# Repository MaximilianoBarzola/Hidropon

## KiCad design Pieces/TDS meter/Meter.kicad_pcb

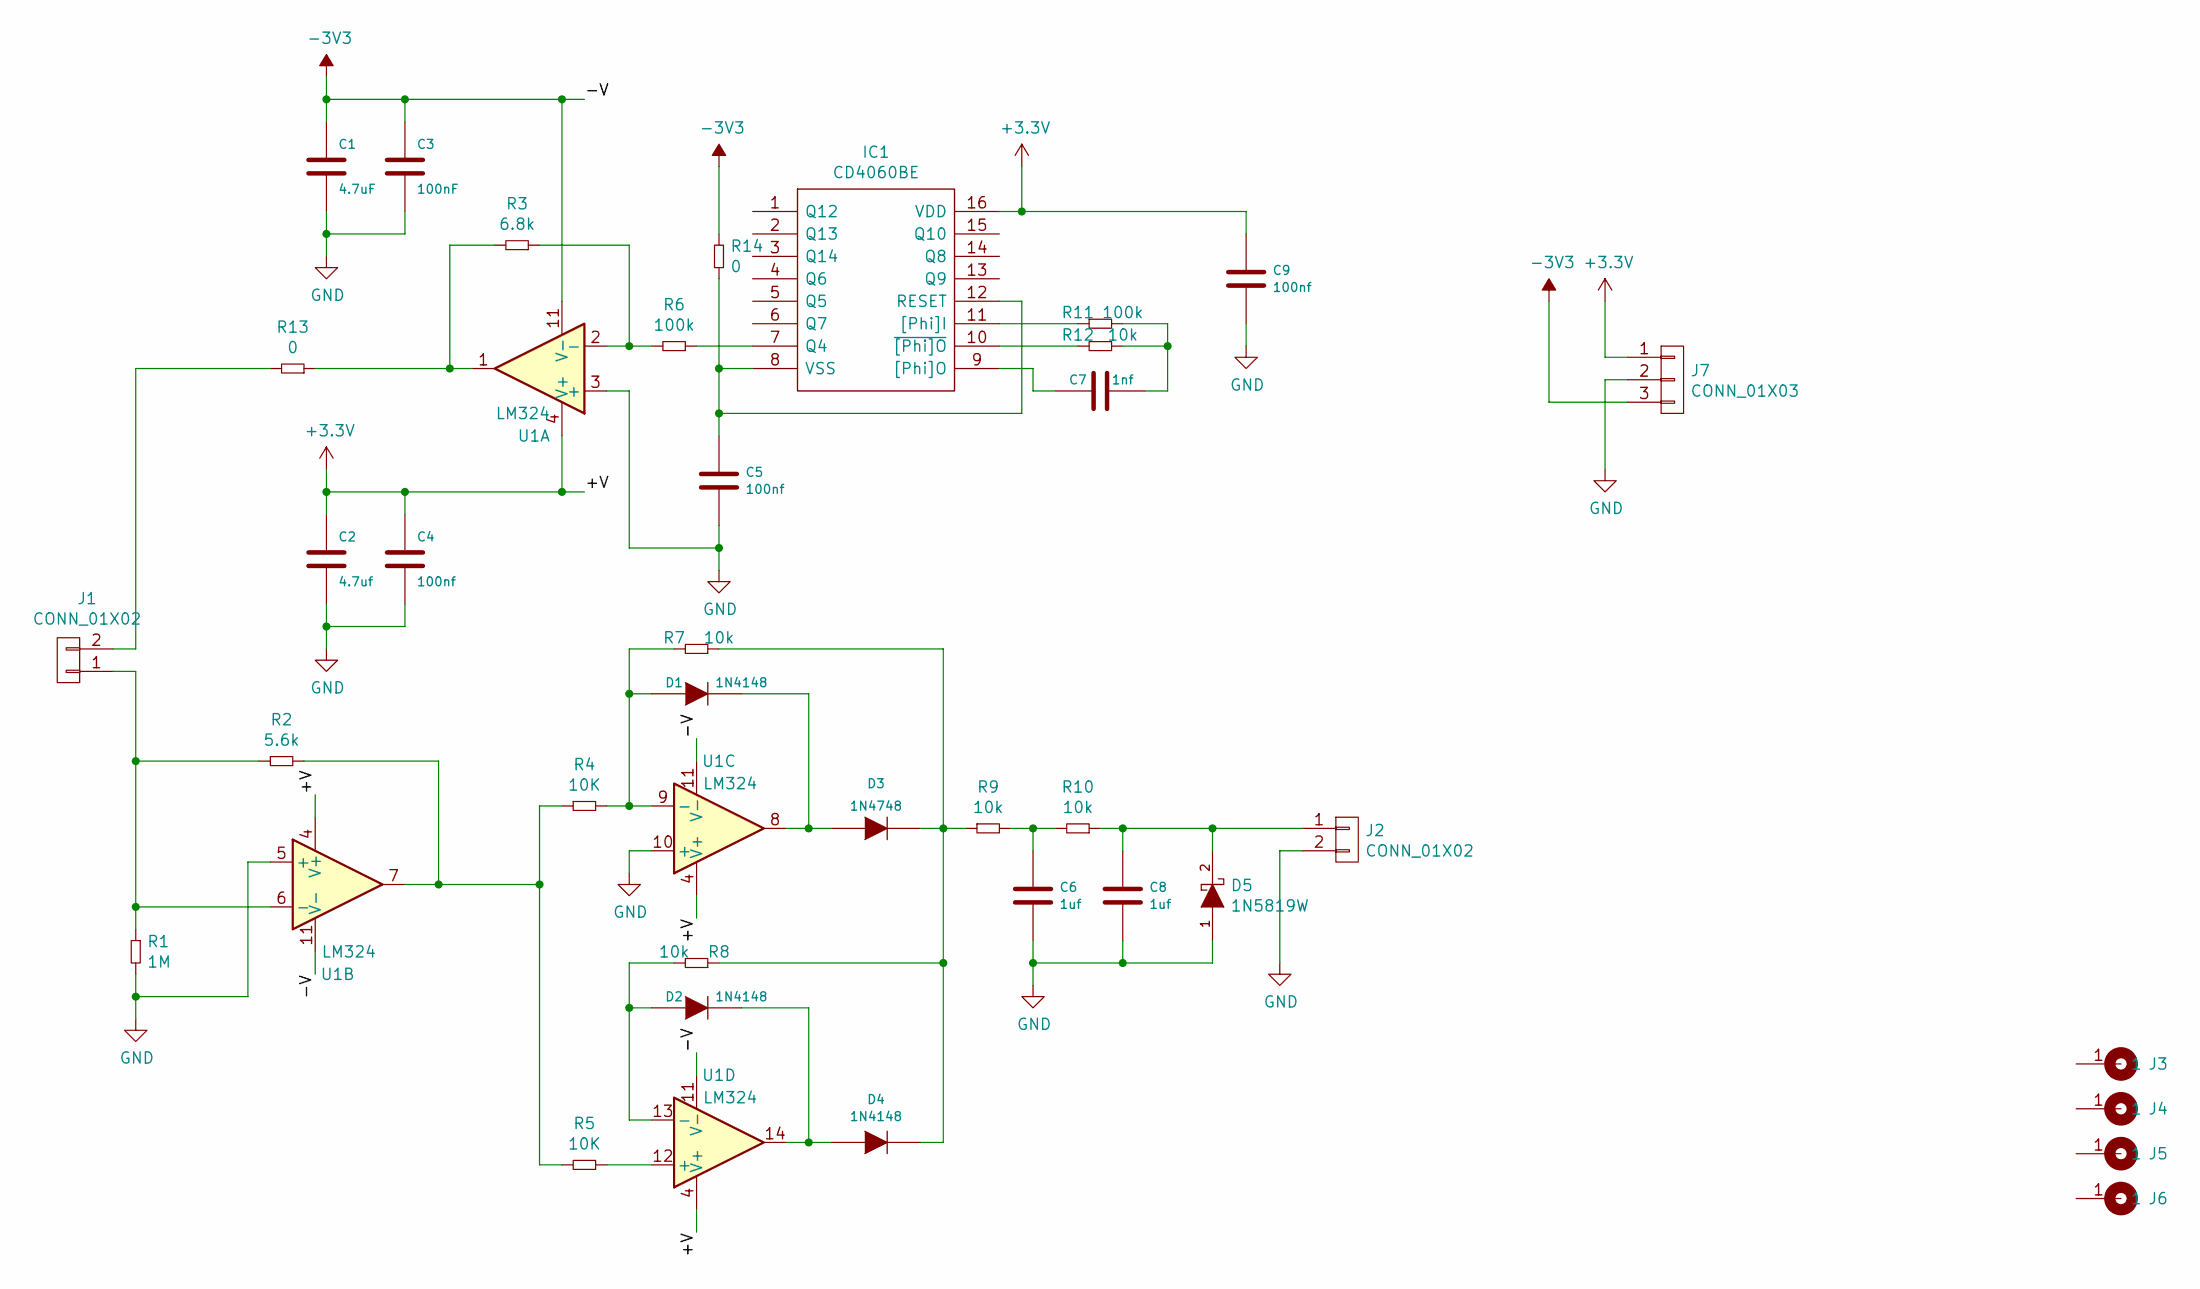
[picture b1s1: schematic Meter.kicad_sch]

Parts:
C1: 4.7uF; C_0805
C2: 4.7uf; C_0805
C3: 100nF; C_0805
C4, C5, C9: 100nf; C_0805
C6, C8: 1uf; C_0805
C7: 1nf; C_0805
D1, D2, D4: 1N4148; SOD80C
D3: 1N4748; SOD80C
D5: 1N5819W; DO-41
IC1: CD4060BE; SOP16; Manufacturer_Part_Number CD4060BE; Mouser Part Number 595-CD4060BE
J1: CONN_01X02; Pin_Strip_2_90
J2: CONN_01X02; Pin_Header_2
J3, J4, J5, J6: Cable_PAD; Tornillo_M3_8mm
J7: CONN_01X03; Pin_Strip_3
R1: 1M; R_0805
R2: 5.6k; R_0805
R3: 6.8k; R_0805
R4: 10K; R_0805
R5: 10K; RES0.3
R6, R11: 100k; R_0805
R7, R8, R9, R10, R12: 10k; R_0805
R13, R14: 0; RES0.3
U1: LM324; SOP14

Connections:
+3V3: C2.1, C4.1, C9.1, IC1.16 (VDD), J7.1, U1.4 (V+)
-3V3: C1.1, C3.1, J7.3, R14.2, U1.11 (V-)
GND: C1.2, C2.2, C3.2, C4.2, C5.2, C6.2, C8.2, C9.2, D5.1 (A), J2.2, J7.2, R1.2, U1.3 (+), U1.5 (+), U1.10 (+)
unnamed: C5.1, IC1.8 (VSS), IC1.12 (RESET), R14.1
unnamed: C6.1, R9.2, R10.2
unnamed: C7.1, R11.2, R12.1
unnamed: C7.2, IC1.9 ([Phi]O)
unnamed: C8.1, D5.2 (K), J2.1, R10.1
unnamed: D1.1 (A), R4.2, R7.2, U1.9 (-)
unnamed: D1.2 (K), D3.1 (A), U1.8
unnamed: D2.1 (A), R8.2, U1.13 (-)
unnamed: D2.2 (K), D4.1 (A), U1.14
unnamed: D3.2 (K), D4.2 (K), R7.1, R8.1, R9.1
unnamed: IC1.7 (Q4), R6.1
unnamed: IC1.10 (~[Phi]O), R12.2
unnamed: IC1.11 ([Phi]I), R11.1
unnamed: J1.1, R1.1, R2.1, U1.6 (-)
unnamed: J1.2, R13.2
unnamed: R2.2, R4.1, R5.2, U1.7
unnamed: R3.1, R6.2, U1.2 (-)
unnamed: R5.1, U1.12 (+)
unnamed: R3.2, R13.1, U1.1

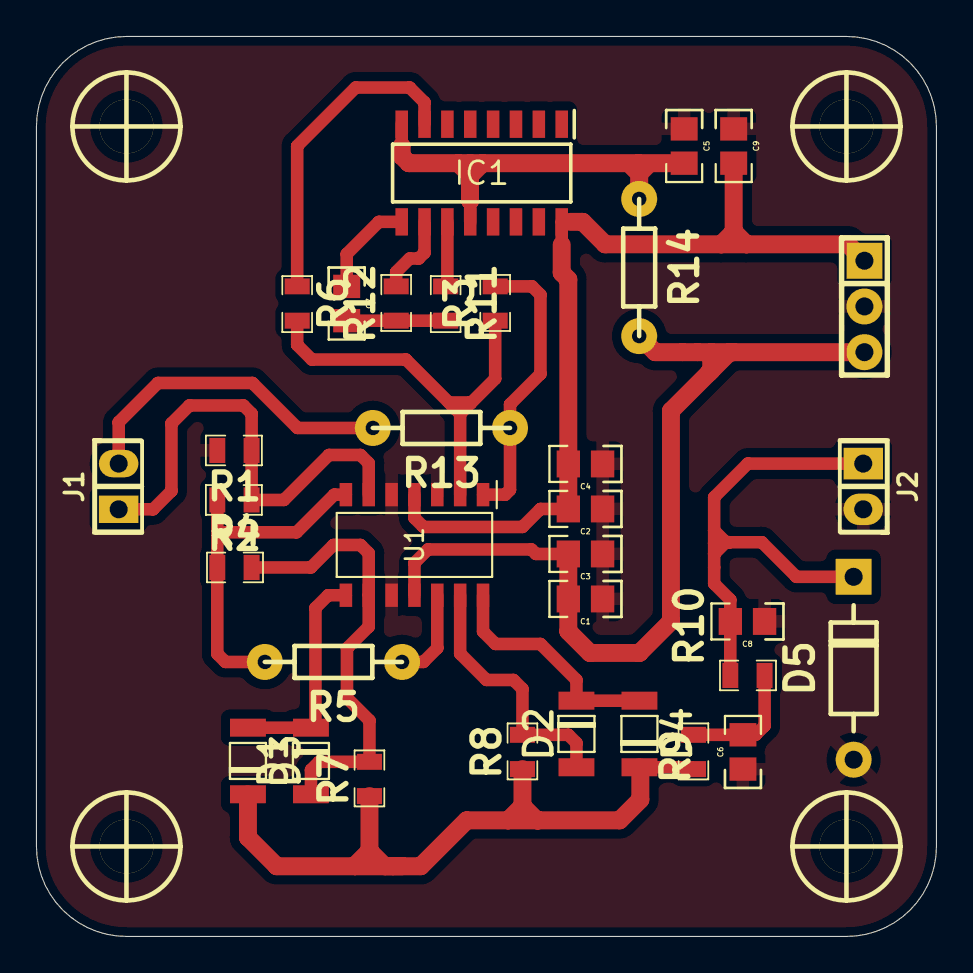
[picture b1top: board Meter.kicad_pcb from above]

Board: 2 copper layers, 50.0 x 50.0 mm, 37 parts (0 on the bottom side), 22 nets.

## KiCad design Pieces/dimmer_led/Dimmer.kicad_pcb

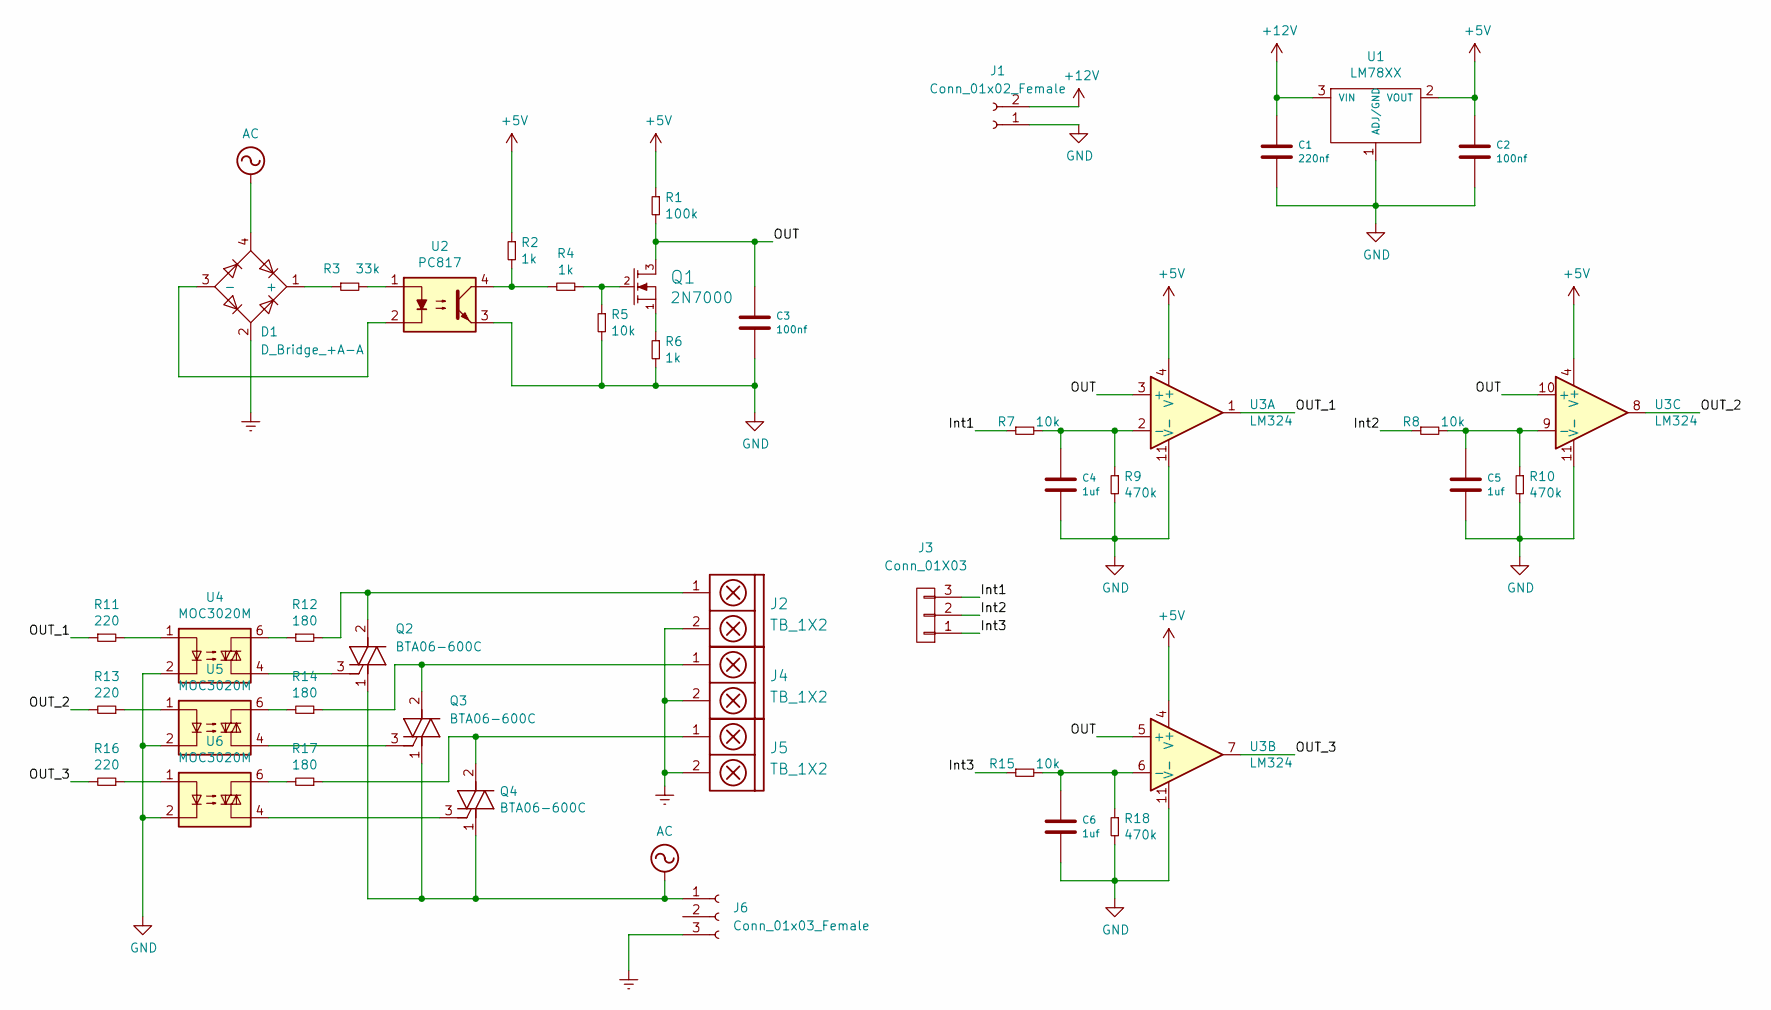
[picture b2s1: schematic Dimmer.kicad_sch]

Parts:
C1: 220nf; CAP_0.1
C2, C3: 100nf; C_0805
C4, C5, C6: 1uf; CAP_0.1
D1: D_Bridge_+A-A; Diode_Bridge_Round_D8.9mm
J1: Conn_01x02_Female; Pin_strip_2
J2, J4, J5: TB_1X2; BORNERA2
J3: Conn_01X03; Pin_Strip_3
J6: Conn_01x03_Female; FanPinHeader_1x03_P2.54mm_Vertical
Q1: 2N7000; to92
Q2, Q3, Q4: BTA06-600C; TO-220-3_Vertical_ac
R1: 100k; R_1206
R2, R4, R6: 1k; RES0.2
R3: 33k; RES0.3
R5, R7, R8, R15: 10k; R_1206
R9, R10, R18: 470k; R_1206
R11, R13, R16: 220; R_0805
R12, R14, R17: 180; R_1206
U1: LM78XX; TO-220-3_Vertical
U2: PC817; DIP-4
U3: LM324; DIP-14
U4, U5, U6: MOC3020M; DIP-6

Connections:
+5V: C2.1, R1.1, R2.1, U1.2 (VOUT), U3.4 (V+)
+12V: C1.1, J1.2, U1.3 (VIN)
/Int1: J3.3, R7.1
/Int2: J3.2, R8.1
/Int3: J3.1, R15.1
/OUT: C3.1, Q1.3 (D), R1.2, U3.3 (+), U3.5 (+), U3.10 (+)
/OUT_1: R11.1, U3.1
/OUT_2: R13.2, U3.8
/OUT_3: R16.2, U3.7
AC: D1.4, J6.1, Q2.1 (A1), Q3.1 (A1), Q4.1 (A1)
Earth: D1.2, J2.2, J4.2, J5.2, J6.3
GND: C1.2, C2.2, C3.2, C4.2, C5.2, C6.2, J1.1, R5.2, R6.2, R9.2, R10.2, R18.2, U1.1 (ADJ/GND), U2.3, U3.11 (V-), U4.2, U5.2, U6.2
unnamed: C4.1, R7.2, R9.1, U3.2 (-)
unnamed: C5.1, R8.2, R10.1, U3.9 (-)
unnamed: C6.1, R15.2, R18.1, U3.6 (-)
unnamed: D1.1 (+), R3.1
unnamed: D1.3 (-), U2.2
unnamed: J2.1, Q2.2 (A2), R12.2
unnamed: J4.1, Q3.2 (A2), R14.1
unnamed: J5.1, Q4.2 (A2), R17.1
unnamed: Q1.1 (S), R6.1
unnamed: Q1.2 (G), R4.1, R5.1
unnamed: Q2.3 (G), U4.4
unnamed: Q3.3 (G), U5.4
unnamed: Q4.3 (G), U6.4
unnamed: R2.2, R4.2, U2.4
unnamed: R3.2, U2.1
unnamed: R11.2, U4.1
unnamed: R12.1, U4.6
unnamed: R13.1, U5.1
unnamed: R14.2, U5.6
unnamed: R16.1, U6.1
unnamed: R17.2, U6.6

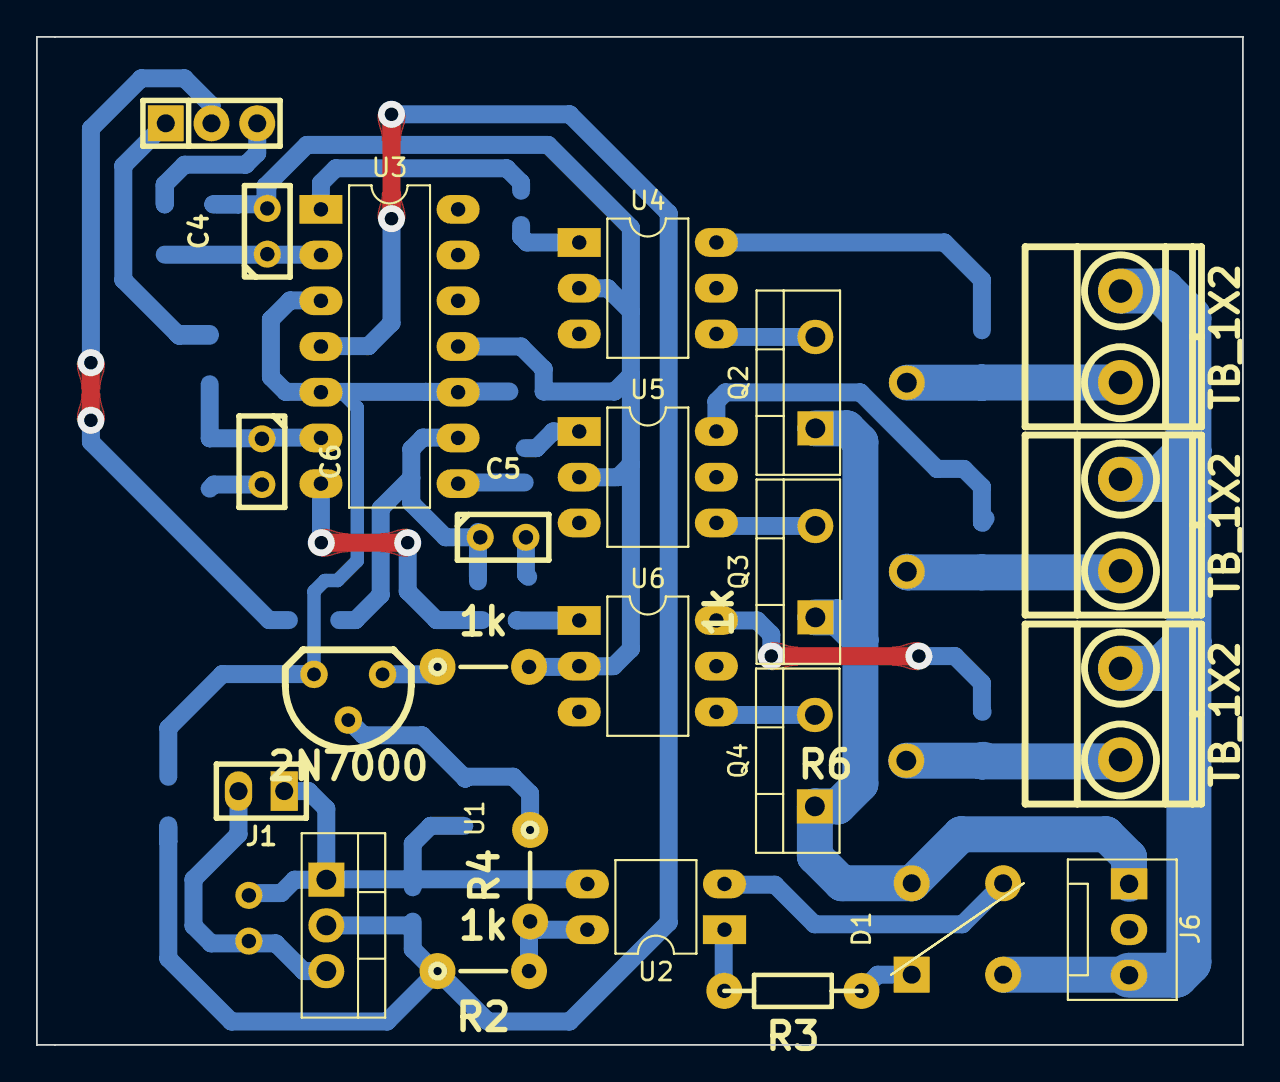
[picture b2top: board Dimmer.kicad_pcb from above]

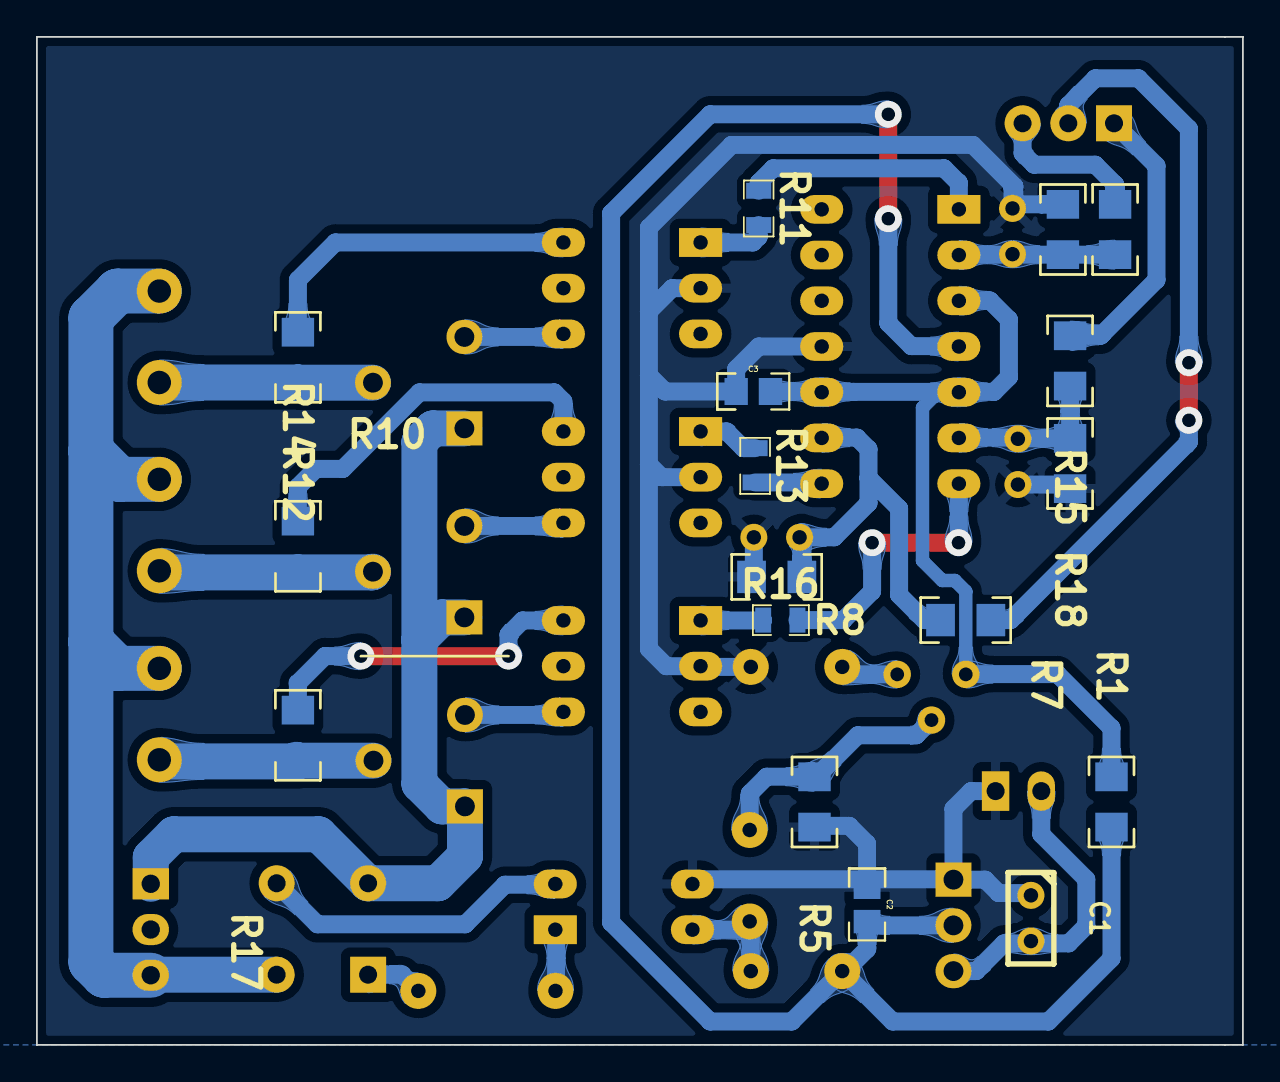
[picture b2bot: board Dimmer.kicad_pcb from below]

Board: 2 copper layers, 67.0 x 56.0 mm, 41 parts (17 on the bottom side), 33 nets.

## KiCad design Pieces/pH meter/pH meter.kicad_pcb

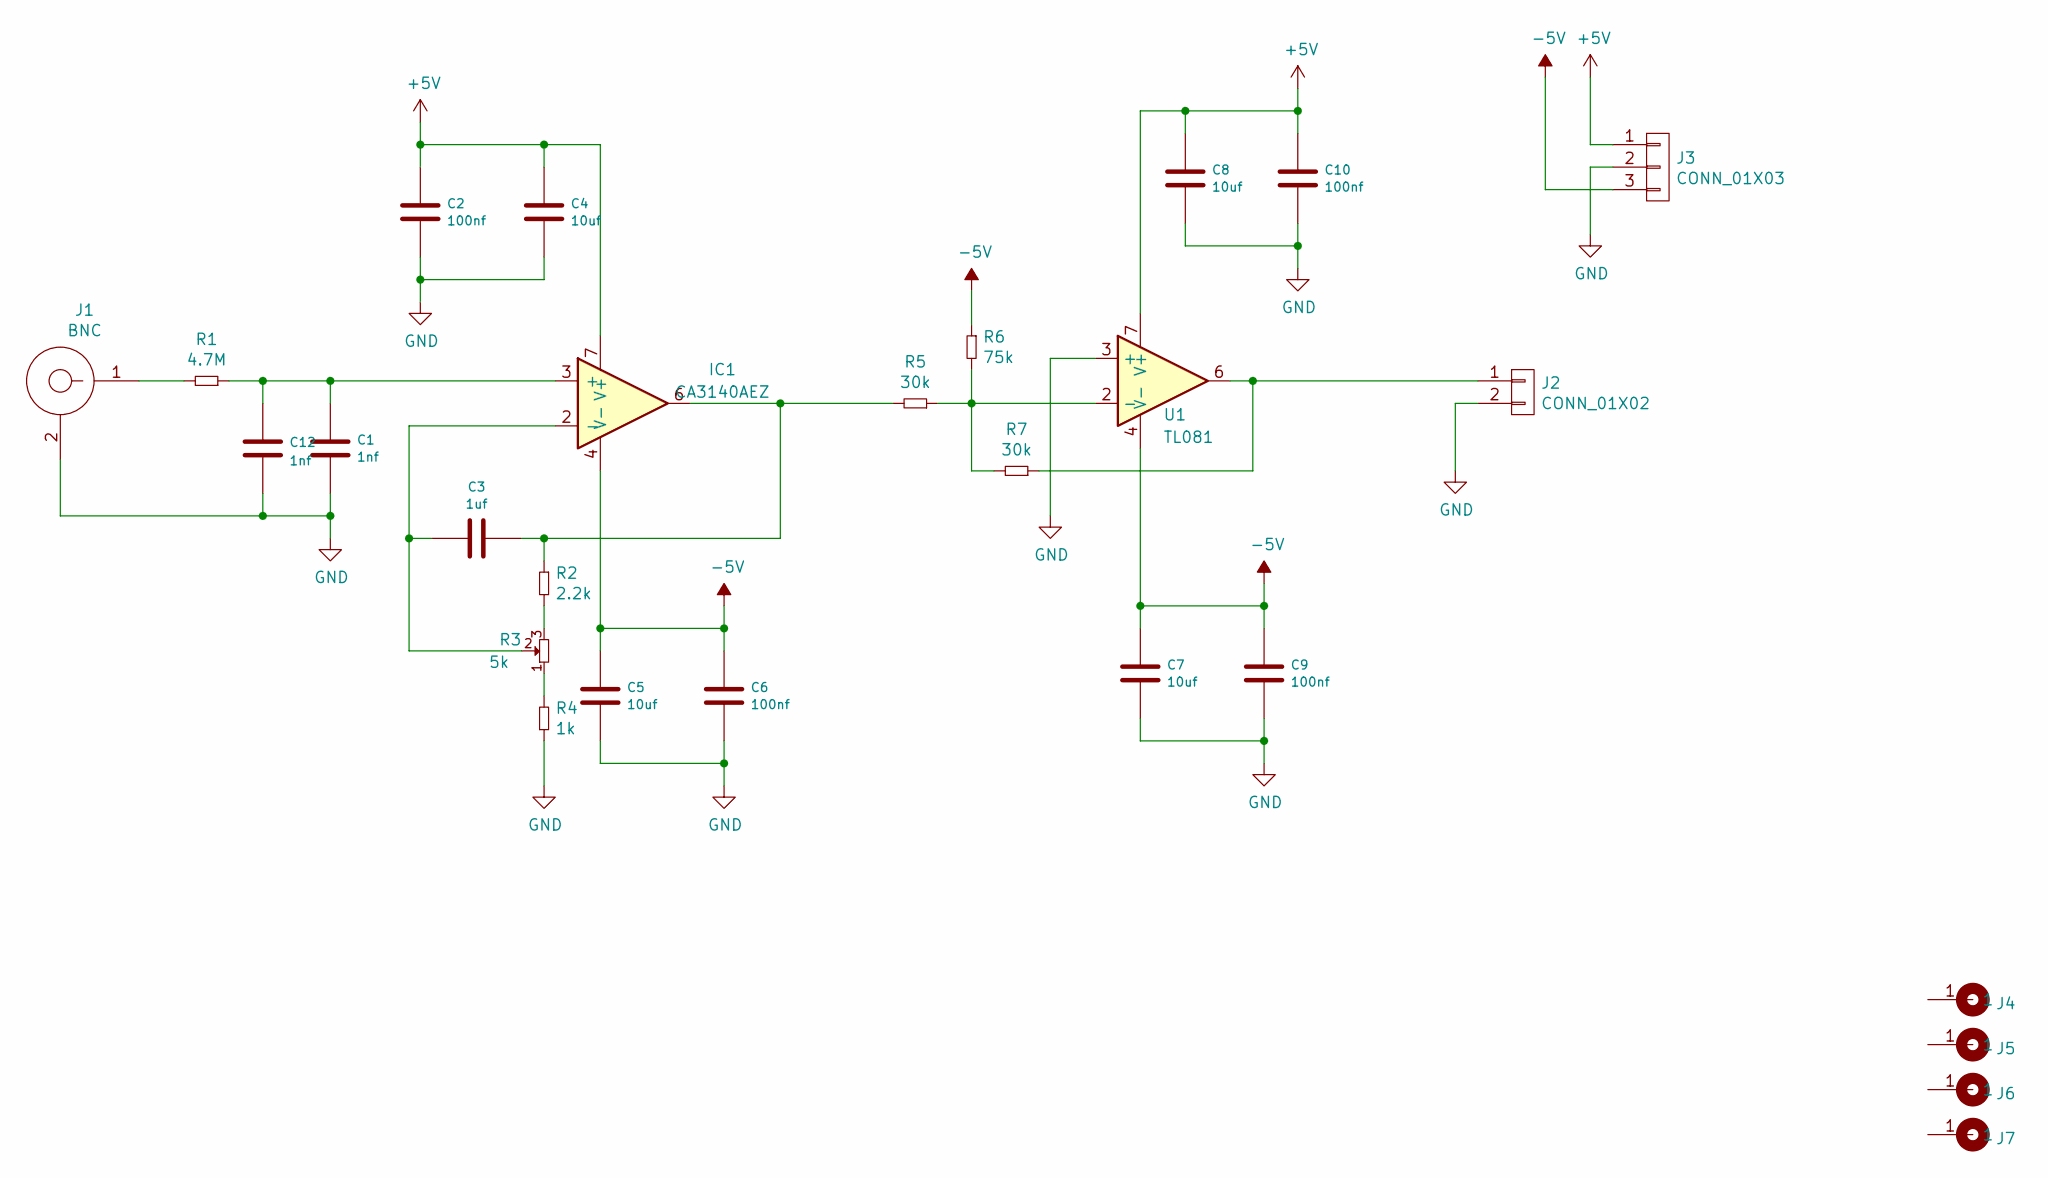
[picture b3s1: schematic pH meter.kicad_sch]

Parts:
C1, C12: 1nf; C_0805
C2, C6, C9, C10: 100nf; C_0805
C3: 1uf; C_0805
C4, C5, C7, C8: 10uf; C_0805
IC1: CA3140AEZ; DIP-8; Manufacturer_Part_Number CA3140AEZ; Mouser Part Number 968-CA3140AEZ
J1: BNC; BNC_Amphenol_B6252HB-NPP3G-50_Horizontal
J2: CONN_01X02; Pin_strip_2
J3: CONN_01X03; Pin_Strip_3
J4, J5, J6, J7: Cable_PAD; Tornillo_M3_8mm
R1: 4.7M; R_0805
R2: 2.2k; RES0.3
R3: 5k; Preset_3296W
R4: 1k; RES0.3
R5: 30k; RES0.3
R6: 75k; RES0.3
R7: 30k; R_0805
U1: TL081; DIP-8

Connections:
+5V: C2.1, C4.1, C8.1, C10.1, IC1.7 (V+), J3.1, U1.7 (V+)
-5V: C5.1, C6.1, C7.1, C9.1, IC1.4 (V-), J3.3, R6.1, U1.4 (V-)
GND: C1.2, C2.2, C4.2, C5.2, C6.2, C7.2, C8.2, C9.2, C10.2, C12.2, J1.2 (GND), J2.2, J3.2, R4.1, U1.3 (+)
unnamed: C1.1, C12.1, IC1.3 (+), R1.1
unnamed: C3.1, IC1.6, R2.1, R5.2
unnamed: C3.2, IC1.2 (-), R3.2
unnamed: J1.1 (OUT), R1.2
unnamed: J2.1, R7.1, U1.6
unnamed: R2.2, R3.3
unnamed: R3.1, R4.2
unnamed: R5.1, R6.2, R7.2, U1.2 (-)

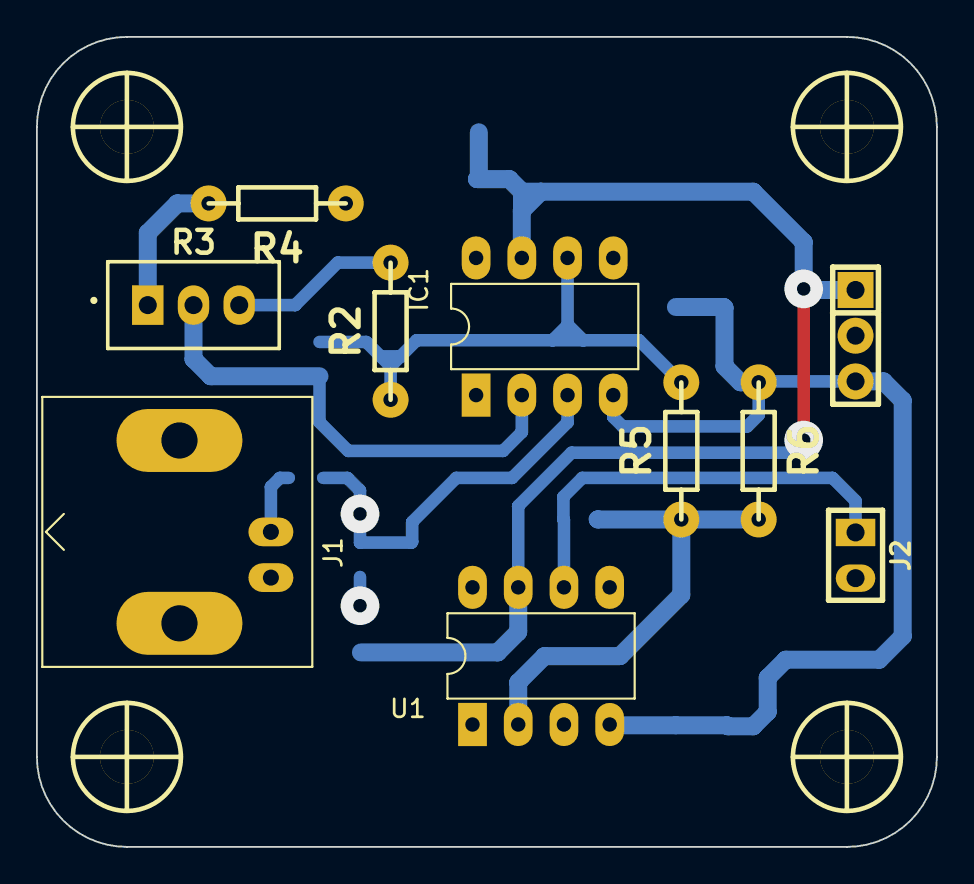
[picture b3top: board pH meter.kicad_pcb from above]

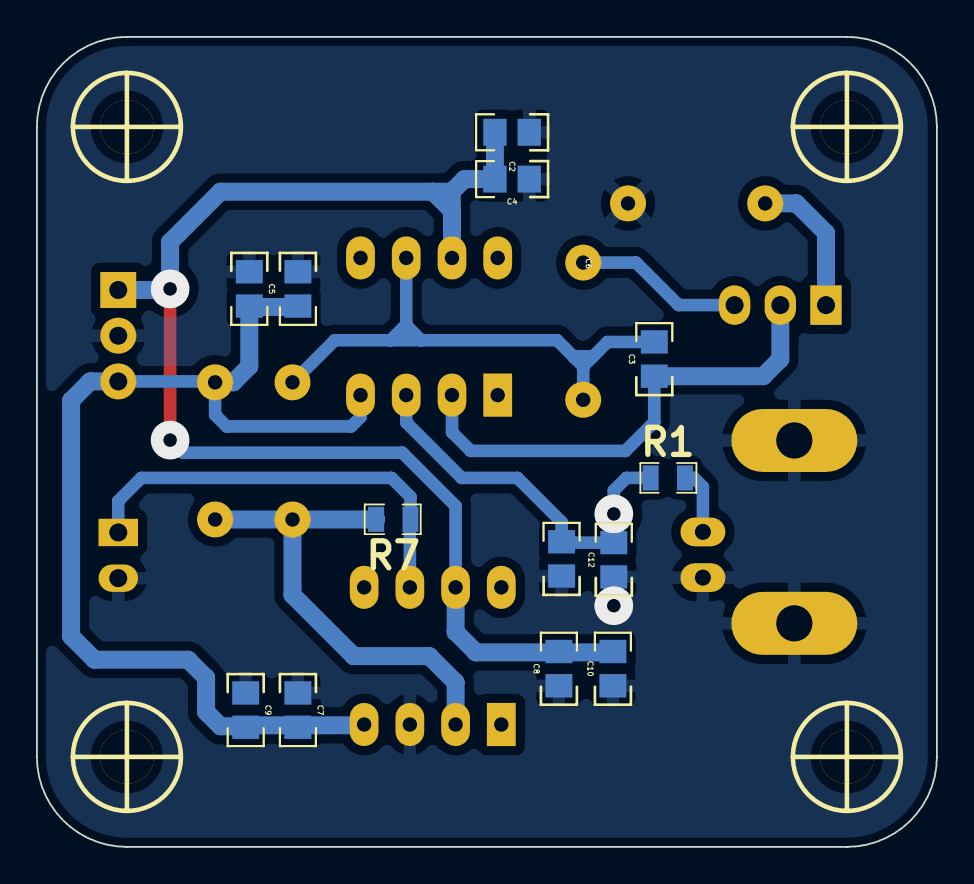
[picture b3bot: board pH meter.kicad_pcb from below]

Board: 2 copper layers, 50.0 x 45.0 mm, 27 parts (13 on the bottom side), 11 nets.

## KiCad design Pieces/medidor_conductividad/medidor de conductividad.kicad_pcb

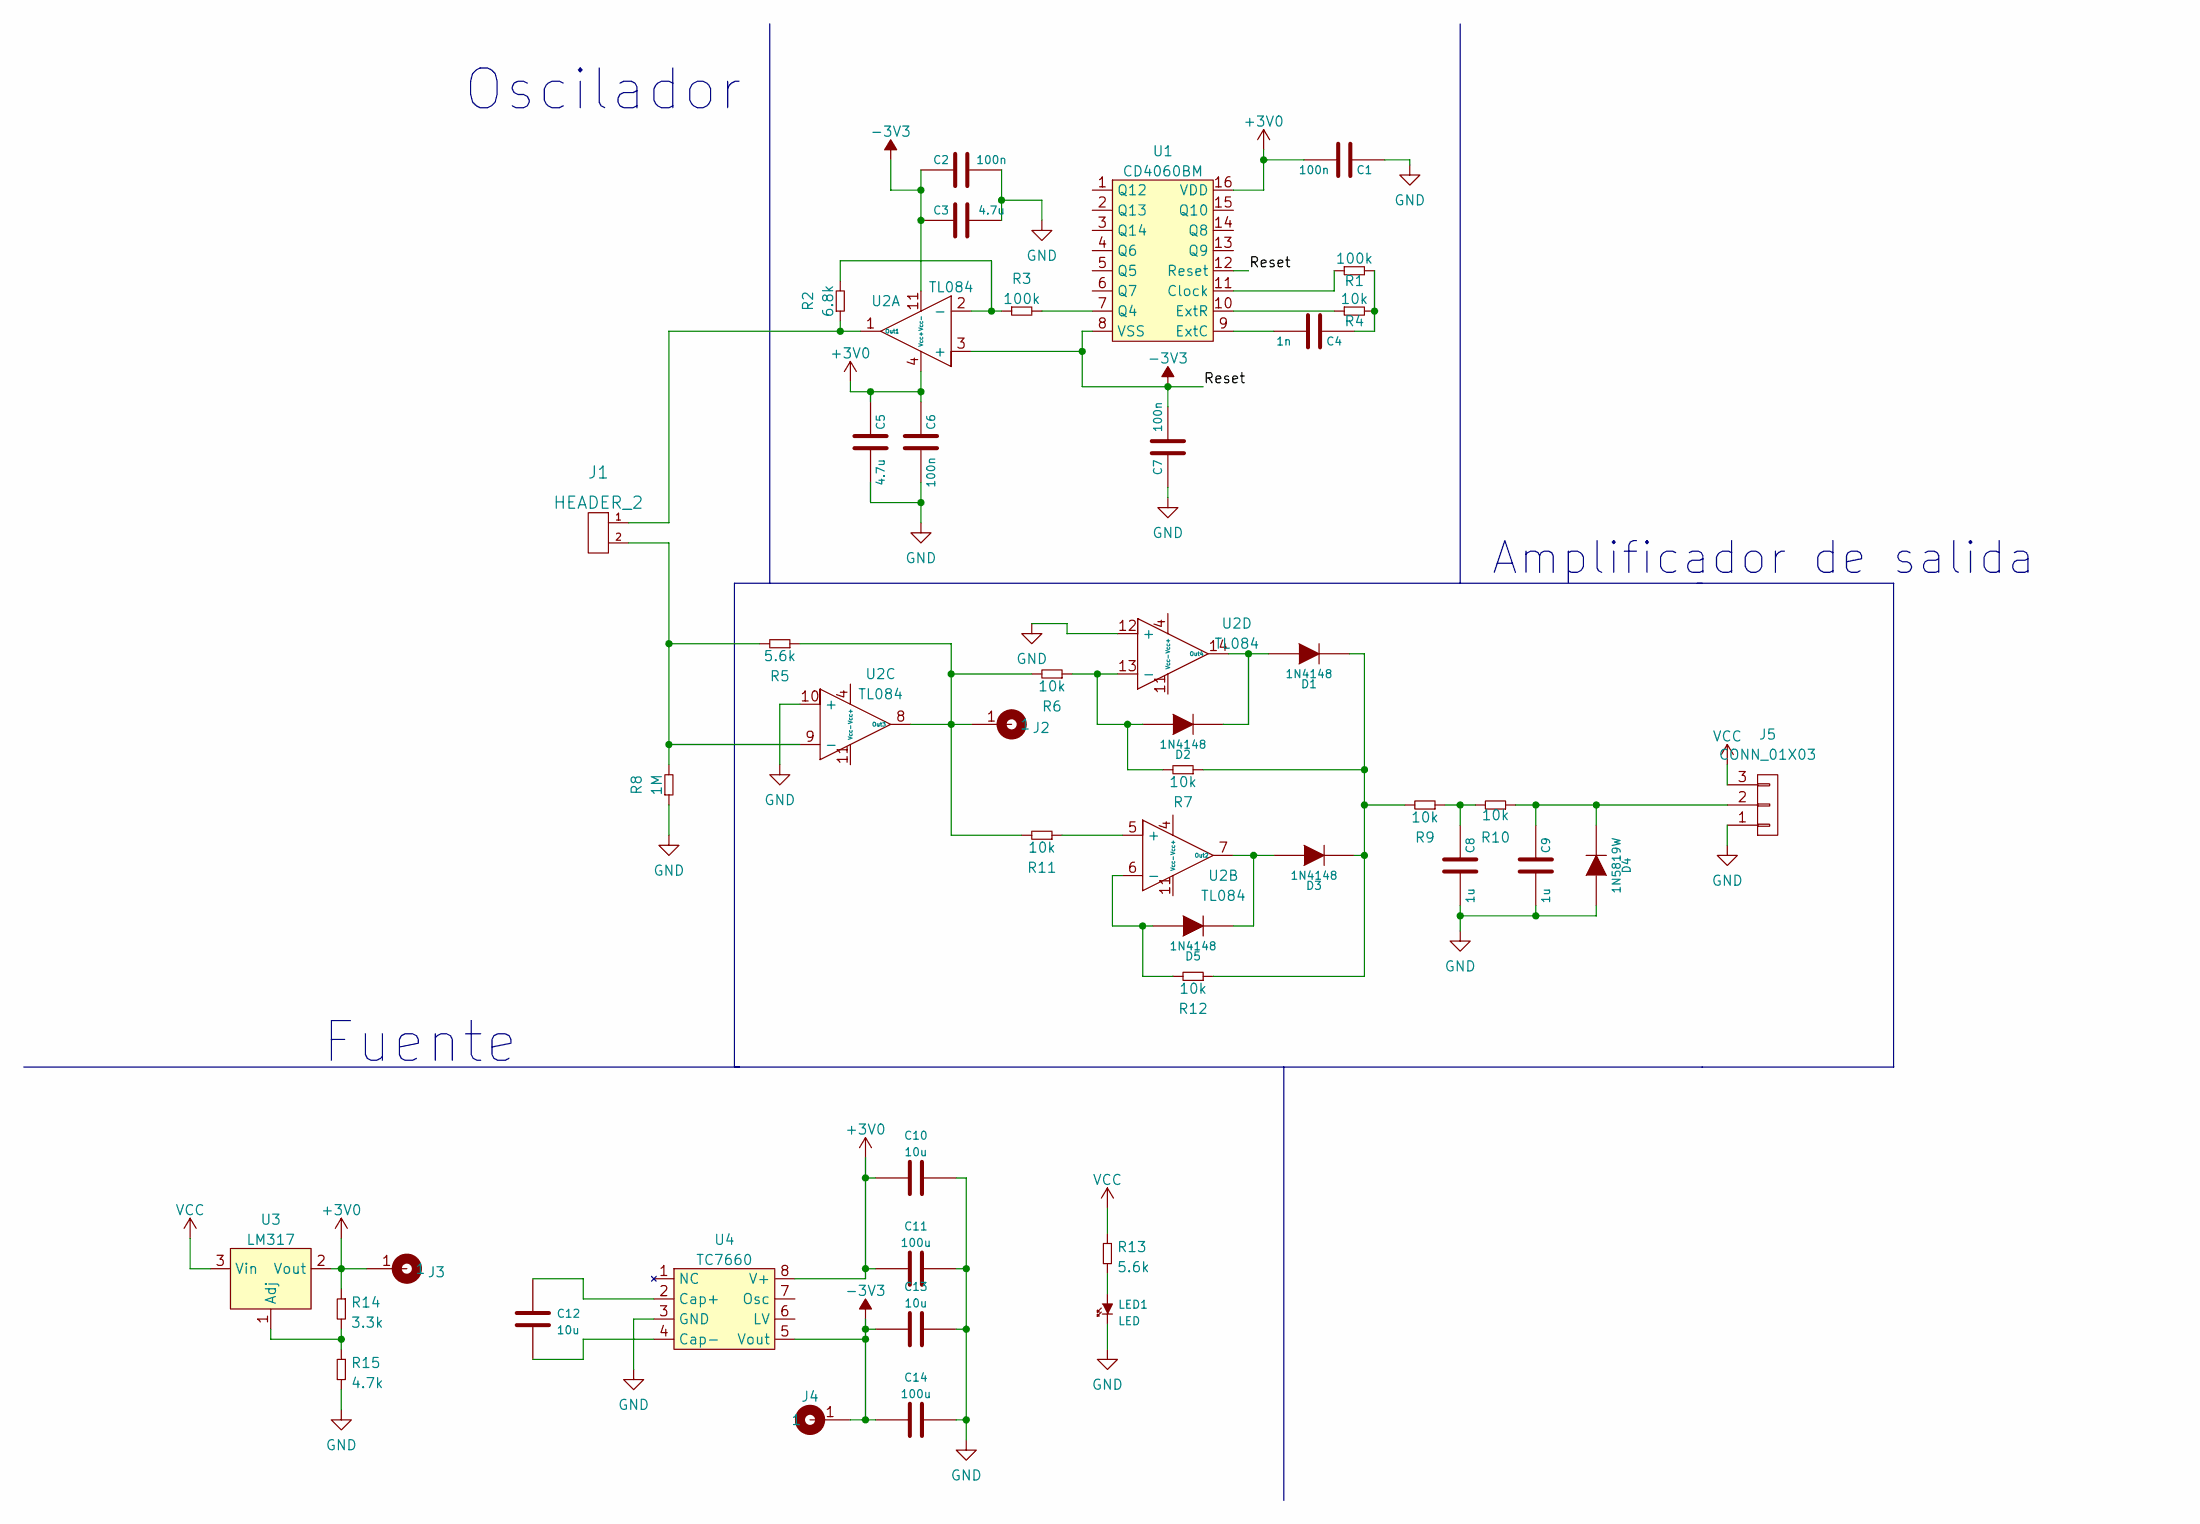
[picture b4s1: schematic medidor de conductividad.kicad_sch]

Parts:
C1, C2, C6, C7: 100n; CAP_0.1
C3, C5: 4.7u; CAP_ELEC_5x11mm
C4: 1n; CAP_0.1
C8, C9: 1u; CAP_ELEC_5x11mm
C10, C12, C13: 10u; CAP_ELEC_5x11mm
C11, C14: 100u; CAP_ELEC_5x11mm
D1, D2, D3, D5: 1N4148; DO-41
D4: 1N5819W; DO-41
J1: HEADER_2; BORNERA2_AZUL
J2, J3, J4: Cable_PAD; Cable_Doble_1,5mm
J5: CONN_01X03; BORNERA3
LED1: LED; led_3mm_red
R1, R3: 100k; RES0.3
R2: 6.8k; RES0.3
R4, R6, R7, R9, R10, R11, R12: 10k; RES0.3
R5, R13: 5.6k; RES0.3
R8: 1M; RES0.3
R14: 3.3k; RES0.3
R15: 4.7k; RES0.3
U1: CD4060BM; DIP-16
U2: TL084; DIP-14
U3: LM317; TO-220-3_Vertical
U4: TC7660; DIP-8

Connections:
+3V0: C1.1, C5.2, C6.2, C10.1, C11.1, J3.1, R14.1, U1.16 (VDD), U2.4 (Vcc+), U3.2 (Vout), U4.8 (V+)
-3V3: C2.2, C3.2, C7.1, C13.1, C14.1, J4.1, U1.8 (VSS), U1.12 (Reset), U2.3 (+), U2.11 (Vcc-), U4.5 (Vout)
GND: C1.2, C2.1, C3.1, C5.1, C6.1, C7.2, C8.1, C9.1, C10.2, C11.2, C13.2, C14.2, D4.1 (A), J5.1, LED1.2 (K), R8.1, R15.2, U2.10 (+), U2.12 (+), U4.3 (GND)
unnamed: C4.1, U1.9 (ExtC)
unnamed: C4.2, R1.2, R4.2
unnamed: C8.2, R9.1, R10.2
unnamed: C9.2, D4.2 (K), J5.2, R10.1
unnamed: C12.1, U4.2 (Cap+)
unnamed: C12.2, U4.4 (Cap-)
unnamed: D1.1 (A), D2.2 (K), U2.14 (Out4)
unnamed: D1.2 (K), D3.2 (K), R7.1, R9.2, R12.1
unnamed: D2.1 (A), R6.1, R7.2, U2.13 (-)
unnamed: D3.1 (A), D5.2 (K), U2.7 (Out2)
unnamed: D5.1 (A), R12.2, U2.6 (-)
unnamed: J1.1, R2.1, U2.1 (Out1)
unnamed: J1.2, R5.2, R8.2, U2.9 (-)
unnamed: J2.1, R5.1, R6.2, R11.2, U2.8 (Out3)
unnamed: LED1.1 (A), R13.2
unnamed: R1.1, U1.11 (Clock)
unnamed: R2.2, R3.1, U2.2 (-)
unnamed: R3.2, U1.7 (Q4)
unnamed: R4.1, U1.10 (ExtR)
unnamed: R11.1, U2.5 (+)
unnamed: R14.2, R15.1, U3.1 (Adj)
VCC: J5.3, R13.1, U3.3 (Vin)

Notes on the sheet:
Amplificador de salida
Fuente
Oscilador

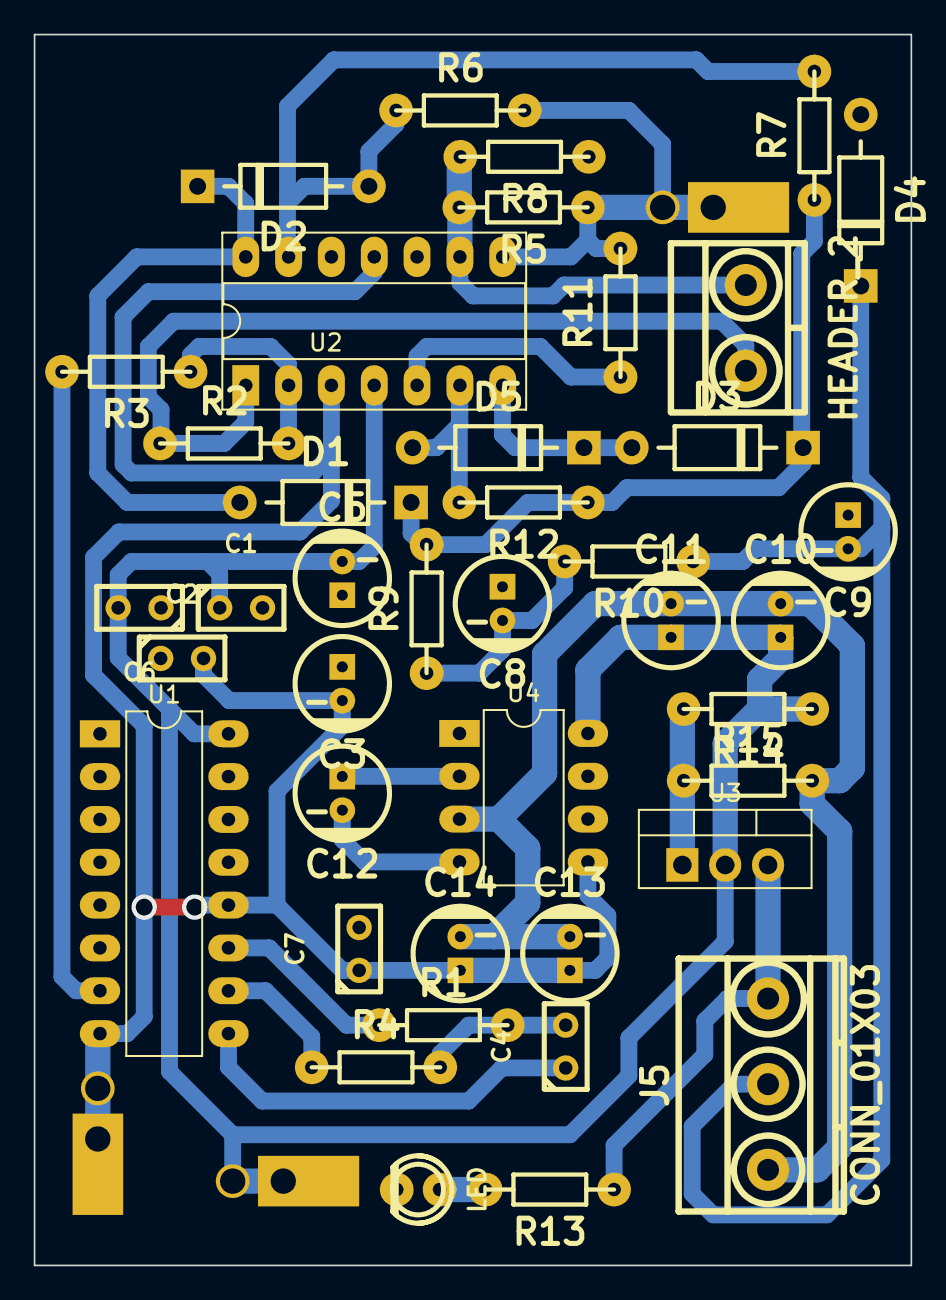
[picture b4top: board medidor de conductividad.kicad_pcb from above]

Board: 2 copper layers, 52.0 x 73.0 mm, 44 parts (0 on the bottom side), 25 nets.
